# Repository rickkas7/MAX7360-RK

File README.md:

# MAX7360-RK

*MAX7360 I2C Keypad, LED, and GPIO for Particle devices*

## Introduction

The [MAX7360](https://www.digikey.com/product-detail/en/maxim-integrated/MAX7360ETL-T/MAX7360ETL-TCT-ND/9760168) is a super-useful keypad, GPIO expander, and LED driver with an I2C interface. The chip is tiny (40TQFN) and a bit expensive ($5.22), but it can do a lot:

- Support for passive matrix keypads up to 8x8. It's perfect for 3x4 phone-style keypads and 4x4 small keypads.
- Built-in debounce (with programmable delay) and FIFO queue for keypad press and release.
- 8 GPIO pins with PWM support.
- Built-in constant-current driver so you don't need current-limiting resistors for LEDs.
- Additional open-drain output ports if you're not using all of the columns.
- Built-in support for LED blink and fade in or out.
- Individual PWM control for up to 8 LEDs.
- Rotary encoder support.
- Debounce support for switches attached to GPIO with programmable delay.
- I2C interface. Addressing support for up to 4 MAX7360 on a single I2C bus.

## The library

Information to be added later.

## KeypadTest Board

I made a simple demo board to test and illustrate the use of the chip. 

Here's the schematic.

And the board layout.

The eagle subdirectory contains the open source design:

- KeypadTest.sch (schematic)
- KeypadTest.brd (board layout)
- KeypadTestv1.zip (gerbers)

### BoM (Bill of Materials)

| Quantity | Item | Example | Price |
| --- | --- | --- | ---: |
| 1 | MAX7360 IC CTRLR KEY-SW I2C 40TQFN | [MAX7360ETL-T](https://www.digikey.com/product-detail/en/maxim-integrated/MAX7360ETL-T/MAX7360ETL-TCT-ND/9760168) | $5.22 |
| 1 | Red LED 5mA 0603 | [Lite-On LTST-C193KRKT-5A](https://www.digikey.com/product-detail/en/lite-on-inc/LTST-C193KRKT-5A/160-1830-1-ND/2356251) | $0.41 |
| 1 | Yellow LED 5mA 0603 | [Lite-On LTST-C193KSKT-5A](https://www.digikey.com/product-detail/en/lite-on-inc/LTST-C193KSKT-5A/160-1831-1-ND/2356253) | $0.41 |
| 1 | Green LED 5mA 0603 | [Lite-On LTST-C193KGKT-5A](https://www.digikey.com/product-detail/en/lite-on-inc/LTST-C193KGKT-5A/160-1828-1-ND/2356247) | $0.41 |
| 3 | 10K Resistor 0603 | [Panasonic ERJ-PA3J103V](https://www.digikey.com/product-detail/en/panasonic-electronic-components/ERJ-PA3J103V/P10KBZCT-ND/5036237) | $0.10 | 
|   | Male header pins 0.1" | [Sullins PRPC040SAAN-RC](https://www.digikey.com/product-detail/en/PRPC040SAAN-RC/S1011EC-40-ND/2775214) |  |

### Other Accessories

The keypad I tested with is the Adafruit [3x4 Phone Matrix Keypad](https://www.adafruit.com/product/1824).

The rotary encoder I tested with is [this one from Amazon](https://www.amazon.com/Cylewet-Encoder-15%C3%9716-5-Arduino-CYT1062/dp/B06XQTHDRR/ref=sr_1_1_sspa). Even though it's listed as being a 5V device, it works well at 3.3V, which is necessary for this design.

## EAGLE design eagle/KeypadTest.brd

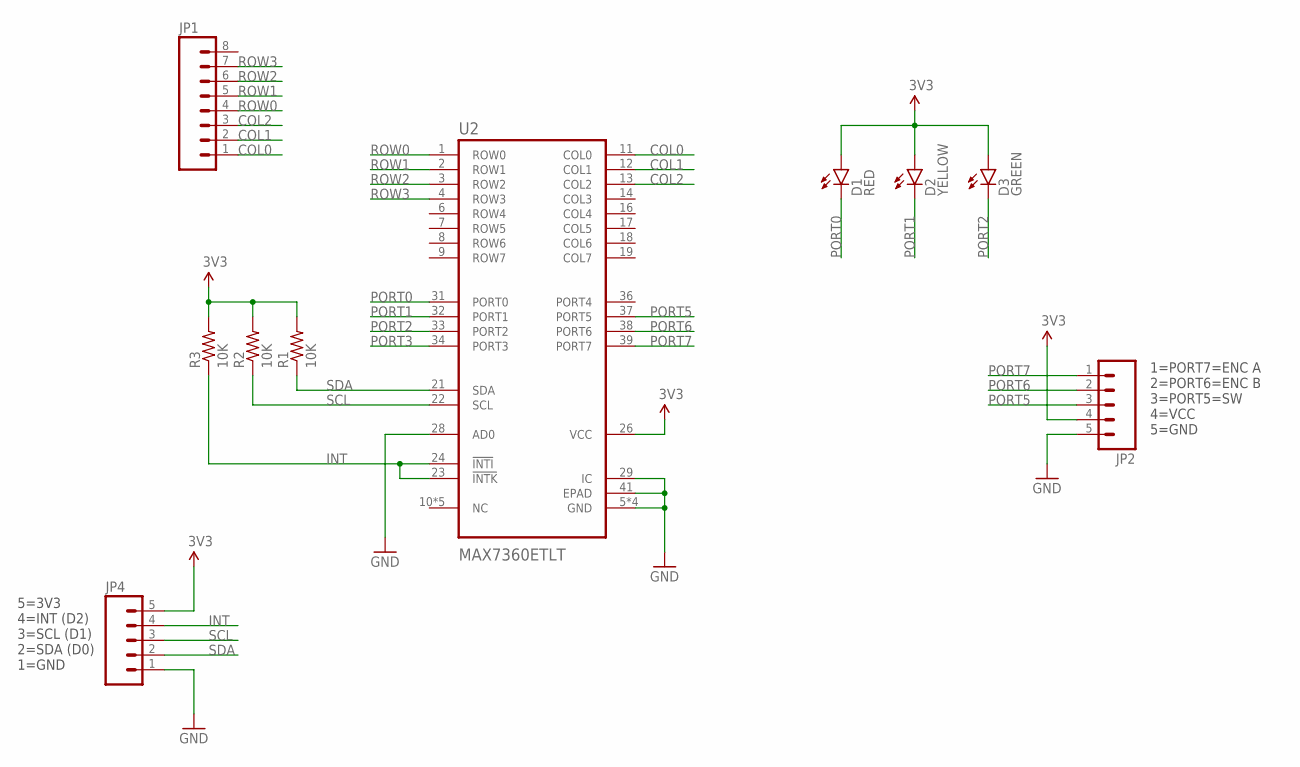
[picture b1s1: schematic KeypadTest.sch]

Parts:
D1: RED; LED-0603
D2: YELLOW; LED-0603
D3: GREEN; LED-0603
JP1: M08SILK_FEMALE_PTH; 1X08
JP2, JP4: M05PTH; 1X05
R1, R2, R3: 10K; 0603-RES
U2: MAX7360ETLT; QFN40P500X500X80-41N

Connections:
3V3: D1.A, D2.A, D3.A, JP2.4, JP4.5, R1.2, R2.2, R3.2, U2.26 (VCC)
COL0: JP1.1, U2.11 (COL0)
COL1: JP1.2, U2.12 (COL1)
COL2: JP1.3, U2.13 (COL2)
GND: JP2.5, JP4.1, U2.5 (GND), U2.15 (GND), U2.25 (GND), U2.28 (AD0), U2.29 (IC), U2.35 (GND), U2.41 (EPAD)
INT: JP4.4, R3.1, U2.23 (!INTK), U2.24 (!INTI)
PORT0: D1.C, U2.31 (PORT0)
PORT1: D2.C, U2.32 (PORT1)
PORT2: D3.C, U2.33 (PORT2)
PORT3: U2.34 (PORT3)
PORT5: JP2.3, U2.37 (PORT5)
PORT6: JP2.2, U2.38 (PORT6)
PORT7: JP2.1, U2.39 (PORT7)
ROW0: JP1.4, U2.1 (ROW0)
ROW1: JP1.5, U2.2 (ROW1)
ROW2: JP1.6, U2.3 (ROW2)
ROW3: JP1.7, U2.4 (ROW3)
SCL: JP4.3, R2.1, U2.22 (SCL)
SDA: JP4.2, R1.1, U2.21 (SDA)

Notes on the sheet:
1=PORT7=ENC A 2=PORT6=ENC B 3=PORT5=SW 4=VCC 5=GND
5=3V3 4=INT (D2) 3=SCL (D1) 2=SDA (D0) 1=GND

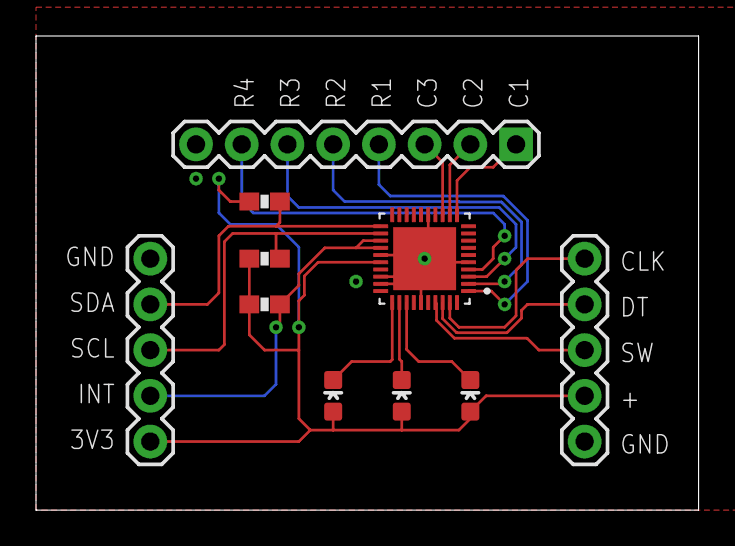
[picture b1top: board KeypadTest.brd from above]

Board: 2 copper layers, 36.8 x 26.3 mm, 10 parts (0 on the bottom side), 18 nets.

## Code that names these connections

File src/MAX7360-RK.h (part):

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	 * - REG_GPO_ENABLE_76543		GPO enable COL7, 6, 5, 4, 3
	 * - REG_GPO_ENABLE_765432		GPO enable COL7, 6, 5, 4, 3, 2 (power-up default)
	 * 
	 * Note that this is different than the PORT2 - PORT7 GPIO!
	 */
	bool setGpoEnable(uint8_t value);

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	static const uint8_t REG_I2C_TIMEOUT_FLAG_MASK			= 0x01;		//!< Bit is set if timeout are enabled (default), and a timeout occurred. Reset on read.


	static const uint8_t REG_GPIO_INPUT						= 0x49;		//!< GPIO (PORT0 - PORT7) values when PORTx is used as input (read-only)
	
	static const uint8_t REG_GPIO_ROTARY_SWITCH_COUNT		= 0x4a;		//!< Rotary switch counter value if enabled (read-only)
	
	// There is no register 0x4b - 0x4f

	static const uint8_t REG_PORT_PWM_RATIO 				= 0x50;		//!< Port PWM ration for PORT0 - PORT7 (registers 0x50 - 0x57)


	static const uint8_t REG_PORT_CONFIG 					= 0x58;		//!< Port config for PORT0 - PORT7 (registers 0x58 - 0x5f)
	static const uint8_t REG_PORT_INTERRUPT_MASK 			= 0x80;		//!< 0 = interrupt disabled (default), 1 = interrupt enabled
	static const uint8_t REG_PORT_EDGE_MASK 				= 0x40;		//!< 0 = rising (default), 1 = rising or falling
	static const uint8_t REG_PORT_COMMON_PWM_MASK	 		= 0x20;		//!< 0 = individual PWM (default), 1 = common PWM
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	static const uint8_t REG_PORT_BLINK_ON_12_5_PCT	 		= 2;		//!< LED on for 12.5% of blink period
	static const uint8_t REG_PORT_BLINK_ON_6_25_PCT	 		= 3;		//!< LED on for 6.25% of blink period

	static const uint8_t PORT7_MASK							= 0b10000000; //!< PORT7 (bit D7) mask
	static const uint8_t PORT6_MASK							= 0b01000000; //!< PORT6 (bit D6) mask
	static const uint8_t PORT5_MASK							= 0b00100000; //!< PORT5 (bit D5) mask
	static const uint8_t PORT4_MASK							= 0b00010000; //!< PORT4 (bit D4) mask
	static const uint8_t PORT3_MASK							= 0b00001000; //!< PORT3 (bit D3) mask
	static const uint8_t PORT2_MASK							= 0b00000100; //!< PORT2 (bit D2) mask
	static const uint8_t PORT1_MASK							= 0b00000010; //!< PORT1 (bit D1) mask
	static const uint8_t PORT0_MASK							= 0b00000001; //!< PORT0 (bit D0) mask

protected:
	/**
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

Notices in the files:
src/MAX7360-RK.h:
License: MIT
